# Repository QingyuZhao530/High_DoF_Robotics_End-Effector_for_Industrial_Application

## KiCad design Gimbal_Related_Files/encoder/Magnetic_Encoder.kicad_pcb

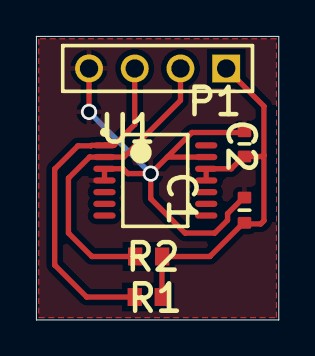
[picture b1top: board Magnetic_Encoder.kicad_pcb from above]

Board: 2 copper layers, 13.5 x 15.7 mm, 6 parts (0 on the bottom side), 4 nets.

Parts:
C1, C2: Capacitor 1µF +/-0.1% 25V 0603; CAPC0603(1608)100_L
P1: TSW-104-08-G-S; SMTC-TSW-104-08-X-S
R1, R2: Resistor 4k7 +/-1% 0603 100 mW; RESC1608X55X25ML10T15
U1: AS5048B-HTSP; AMS-TSSOP-14-5000X4400DE_L

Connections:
+3V3: C1.2, C2.2, P1.1, R1.2, R2.2, U1.11, U1.12
GND: C1.1, C2.1, P1.4, U1.3, U1.4, U1.13
SCL: P1.2, R2.1, U1.2
SDA: P1.3, R1.1, U1.1

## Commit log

2026-04-22 update demo pics and videos
2026-04-22 Rename Magnetic_Encoder.kicad_sch to Gimbal_Related_Files/encoder/Magnetic_Encoder.kicad_sch
2026-04-22 Rename Magnetic_Encoder-altium-import.kicad_sym to Gimbal_Related_Files/encoder/Magnetic_Encoder-altium-import.kicad_sym
2026-04-22 Rename Magnetic_Encoder.kicad_pcb to Gimbal_Related_Files/encoder/Magnetic_Encoder.kicad_pcb
2026-04-22 Rename sym-lib-table to Gimbal_Related_Files/encoder/sym-lib-table
